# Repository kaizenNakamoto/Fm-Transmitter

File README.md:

# Fm-Transmitter
CT1 project  
SIMPLE FM transmitter PCB design using eagle  
SCHEMATIC - https://imgur.com/Txk5Rgm

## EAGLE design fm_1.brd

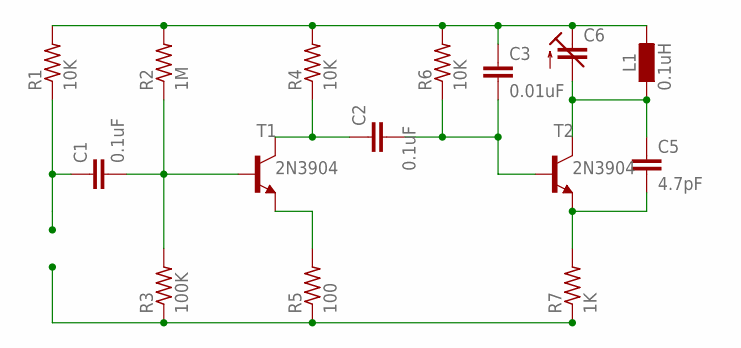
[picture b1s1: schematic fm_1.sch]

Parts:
C1, C2: 0.1uF; C025-040X050
C3: 0.01uF; C025-040X050
C5: 4.7pF; C025-040X050
C6: C-TRIMM808; CTRIM808-BC
L1: 0.1uH; 0204/7
R1, R4, R6: 10K; 0204V
R2: 1M; 0204V
R3: 100K; 0204V
R5: 100; 0204V
R7: 1K; 0204V
T1, T2: 2N3904; TO92

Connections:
unnamed: C3.1, C6.1 (E), L1.1, R1.2, R2.2, R4.2, R6.2
unnamed: C1.1, R1.1
unnamed: C1.2, R2.1, R3.2, T1.2 (B)
unnamed: R3.1, R5.1, R7.1
unnamed: C2.1, R4.1, T1.1 (C)
unnamed: C2.2, C3.2, R6.1, T2.2 (B)
unnamed: C5.1, C6.2 (A), L1.2, T2.1 (C)
unnamed: C5.2, R7.2, T2.3 (E)
unnamed: R5.2, T1.3 (E)

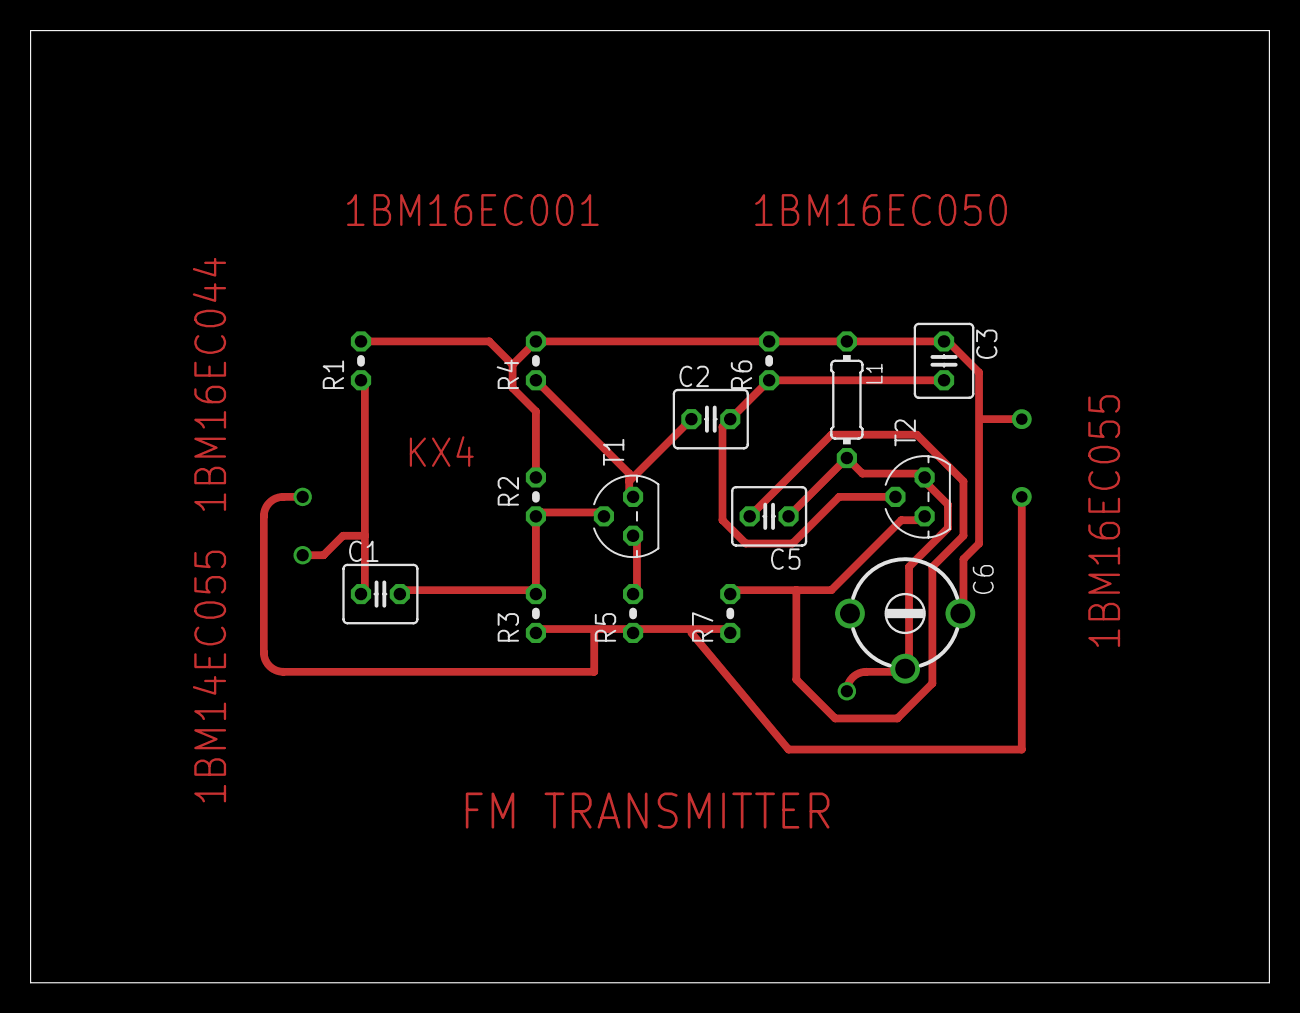
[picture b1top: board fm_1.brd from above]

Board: 2 copper layers, 81.0 x 62.2 mm, 15 parts (0 on the bottom side), 9 nets.

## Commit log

2018-11-15 Routing Done
2018-11-16 changed to 3pin Trimmer Cap + USN's corrected
2018-11-22 New design
2018-11-22 Updated Design
